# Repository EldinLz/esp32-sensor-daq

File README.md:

# ESP32 Sensor Data Acquisition Board

A custom two-layer PCB and Arduino firmware project for collecting ambient-light, temperature, humidity, and pressure data with an ESP32-C3.

> **Project status:** Rev A was hand-assembled, programmed, and hardware-validated on 2026-08-22. The ESP32-C3 streams serial CSV data, the BME280 is detected over I2C, and the MCP6002-buffered light channel responds from covered to bright-light conditions. Long-duration logging and calibrated light measurement have not been completed.

## Overview

This project combines a custom KiCad carrier board with an ESP32-C3 DevKitM-1. A photoresistor signal is conditioned by an MCP6002 op-amp and sampled by the ESP32 ADC, while a BME280 breakout provides environmental data over I2C. Six labeled test points expose the primary power and signal nets for structured bring-up and debugging.

```mermaid
flowchart LR
    LDR["Photoresistor divider"] --> OP["MCP6002 buffer"]
    OP --> ADC["ESP32-C3 GPIO0 / ADC"]
    BME["BME280 temperature, humidity, pressure"] -->|"I2C: GPIO4 SDA, GPIO5 SCL"| ESP["ESP32-C3"]
    ADC --> ESP
    ESP --> LED["Status LED on GPIO7"]
    ESP --> USB["CSV data over USB serial"]
```

## Finished hardware

The Rev A PCB was assembled by hand with the ESP32-C3 in removable socket headers and the BME280 connected through the labeled J1 I2C header.

## Key features

- ESP32-C3 DevKitM-1 controller on removable 1x15 sockets
- BME280 interface with 4.7 kOhm I2C pull-up resistors
- Photoresistor voltage divider buffered by an MCP6002 op-amp
- 100 nF local decoupling capacitor for the analog section
- Status LED with a 330 Ohm current-limiting resistor
- Six labeled test points: 3V3, GND, raw light signal, buffered ADC signal, SDA, and SCL
- CSV serial output suitable for logging or plotting
- Through-hole construction for accessible hand assembly and rework

## Pin map

| Function | ESP32-C3 pin | PCB test point or connector |
|---|---:|---|
| Light sensor ADC | GPIO0 | TP4 `ADC` |
| I2C SDA | GPIO4 | TP5 `SDA`, J1 pin 3 |
| I2C SCL | GPIO5 | TP6 `SCL`, J1 pin 4 |
| Status LED | GPIO7 | D1 through R5 |
| 3.3 V | 3V3 | TP1, J1 pin 1 |
| Ground | GND | TP2, J1 pin 2 |
| Raw light-divider signal | - | TP3 `RAW` |

## Firmware

The Arduino firmware:

1. Initializes the ESP32 ADC and the BME280 at address `0x77`, then tries `0x76` as a fallback.
2. Samples the buffered light-sensor signal once per second.
3. Reads temperature, humidity, and pressure when the BME280 is available.
4. Emits one CSV row per second at 115200 baud.

Measured Rev A serial output:

```text
BME280 detected
time_ms,light_raw,light_percent,temperature_C,humidity_percent,pressure_hPa
628,2058,50.3,25.70,47.22,1009.73
```

### Build environment

- Arduino IDE 2.3.10
- `esp32` board package by Espressif Systems 3.3.11
- Board target: `ESP32C3 Dev Module`
- Adafruit BME280 Library 2.3.0 and its installed dependencies

## Rev A hardware validation

These captured values demonstrate end-to-end operation; they are not calibration data.

| Check | Result | Captured evidence |
|---|---|---|
| Post-assembly power-off check | Pass | No 3V3-to-GND short was found. |
| 3.3 V operation | Pass | The assembled board powered and ran from the ESP32-C3 3.3 V rail. |
| Firmware and serial output | Pass | Firmware uploaded successfully and produced one 115200-baud CSV row per second. |
| BME280 I2C sensing | Pass | Serial Monitor reported `BME280 detected`; observed readings were about 25.2-26.0 C, 47-49% RH, and 1009.7-1009.9 hPa. |
| Light channel - covered | Pass | `light_raw` approximately 247-265; `light_percent` approximately 6.0-6.5%. |
| Light channel - room light | Pass | `light_raw` approximately 1887-2134; `light_percent` approximately 46.1-52.1%. |
| Light channel - flashlight | Pass | `light_raw` = 4095; `light_percent` = 100.0%. |
| Status LED | Pass | A brief firmware-driven activity blink was observed. |

`light_percent` is the 12-bit ADC reading normalized to full scale; it is not a calibrated lux measurement. The light tests validate the complete photoresistor-divider, MCP6002-buffer, ADC, firmware, and serial-output path, but do not independently characterize the op-amp transfer function.

See [VALIDATION.md](docs/VALIDATION.md) for the full validation record and [TEST_PLAN.md](docs/TEST_PLAN.md) for the staged bring-up procedure.

## Repository structure

```text
.
├── fabrication/  Final Gerber and drill archive used for PCB ordering
├── firmware/     Arduino sketch folder and firmware source
├── hardware/     KiCad schematic, PCB, and project files
├── images/       KiCad renders and finished Rev A build photos
└── docs/         BOM, validation record, test plan, and resume notes
```

## Design and validation status

- KiCad schematic ERC: 0 errors and 0 warnings
- KiCad PCB Editor DRC: 0 errors; one expected footprint/library mismatch warning after the ESP32 socket-pad customization
- Unrouted connections: 0
- Gerber and drill archive generated; PCB fabrication and delivery complete
- Rev A assembly, soldering, post-assembly short check, firmware upload, and serial output: complete
- BME280 I2C sensing and end-to-end light-channel response: hardware-validated

## Optional follow-on characterization

- Run and archive a one-hour serial logging test
- Measure TP3 (`RAW`) and TP4 (`ADC`) simultaneously to quantify buffer tracking
- Calibrate the light channel against a lux reference if absolute illumination is required

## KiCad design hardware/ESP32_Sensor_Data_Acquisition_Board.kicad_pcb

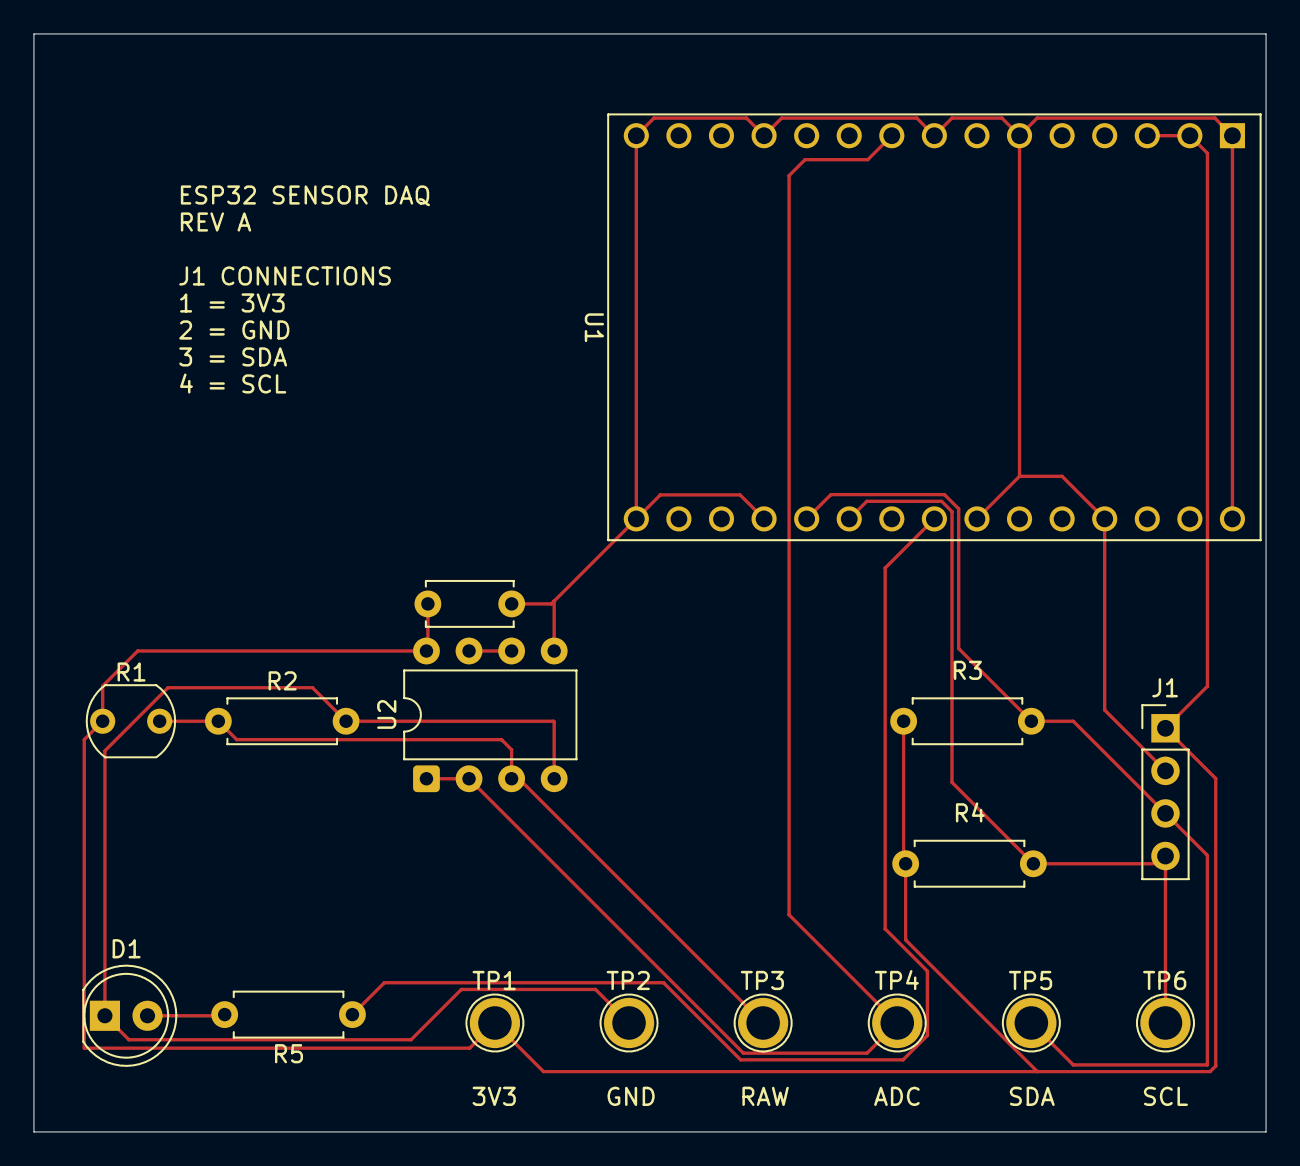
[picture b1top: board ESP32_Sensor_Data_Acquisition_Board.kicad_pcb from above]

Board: 2 copper layers, 73.5 x 65.5 mm, 16 parts (0 on the bottom side), 9 nets.

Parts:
C1: 100nF; C_Disc_D5.0mm_W2.5mm_P5.00mm
D1: LED; LED_D5.0mm
J1: BME280; PinHeader_1x04_P2.54mm_Vertical
R1: R_Photo; R_LDR_5.1x4.3mm_P3.4mm_Vertical
R2: 10k; R_Axial_DIN0207_L6.3mm_D2.5mm_P7.62mm_Horizontal
R3, R4: 4.7k; R_Axial_DIN0207_L6.3mm_D2.5mm_P7.62mm_Horizontal
R5: 330; R_Axial_DIN0207_L6.3mm_D2.5mm_P7.62mm_Horizontal
TP1, TP2, TP3, TP4, TP5, TP6: TestPoint; TestPoint_Plated_Hole_D2.0mm
U1: ESP32-C3-DevKitM-1
U2: MCP6002-xP; DIP-8_W7.62mm

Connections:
+3V3: C1.1, J1.1, R1.1, R3.1, R4.1, TP1.1 (1_1), U1.2 (3V3), U1.3 (3V3), U2.8 (V+)
/I2C_SCL: J1.4, R4.2, TP6.1 (1_1), U1.21 (IO5)
/I2C_SDA: J1.3, R3.2, TP5.1 (1_1), U1.20 (IO4)
/LIGHT_ADC: TP4.1 (1_1), U1.9 (IO0), U2.1, U2.2 (-)
/LIGHT_RAW: R1.2, R2.1, TP3.1 (1_1), U2.3 (+)
/STATUS_LED: R5.1, U1.23 (IO7)
GND: C1.2, D1.1 (K), J1.2, R2.2, TP2.1 (1_1), U1.1 (GND), U1.6 (GND), U1.8 (GND), U1.12 (GND), U1.15 (GND), U1.16 (GND), U1.19 (GND), U1.24 (GND), U1.27 (GND), U1.30 (GND), U2.4 (V-), U2.5 (+)
unnamed: D1.2 (A), R5.2
unnamed: U2.6 (-), U2.7

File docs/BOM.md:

# Bill of Materials

Quantities below are for one assembled board. Exact supplier stock can change; verify the footprint, lead pitch, and voltage rating before substituting a part.

| Ref. | Qty. | Component | Value / selected part | PCB footprint or interface |
|---|---:|---|---|---|
| U1 | 1 | ESP32-C3 development board | ESP32-C3 DevKitM-1 | Two 1x15, 2.54 mm socket rows |
| U2 | 1 | Dual rail-to-rail op-amp | MCP6002-I/P | DIP-8, 7.62 mm row spacing |
| — | 1 | DIP socket | 8-position | DIP-8 |
| R1 | 1 | CdS photoresistor | 5 mm class | 3.4 mm lead pitch footprint |
| R2 | 1 | Resistor | 10 kΩ, 1/4 W | Axial, 7.62 mm pitch |
| R3, R4 | 2 | I2C pull-up resistors | 4.7 kΩ, 1/4 W | Axial, 7.62 mm pitch |
| R5 | 1 | LED resistor | 330 Ω, 1/4 W | Axial, 7.62 mm pitch |
| C1 | 1 | Ceramic capacitor | 100 nF | Through-hole disc, 5.00 mm pitch |
| D1 | 1 | Status LED | 5 mm LED | 2.54 mm pitch |
| J1 | 1 | BME280 connector | 1x4 vertical pin header | 2.54 mm pitch |
| — | 1 | BME280 breakout | Adafruit BME280 I2C/SPI breakout | Connected to J1 over 3V3, GND, SDA, SCL |
| — | 2 | ESP32 socket strips | 1x15 female receptacle | 2.54 mm pitch |

## Test points

TP1 through TP6 are plated through-holes and do not require a separate component. Optional loop or turret test points may be installed if desired.

| Test point | Net |
|---|---|
| TP1 | 3V3 |
| TP2 | GND |
| TP3 | LIGHT_RAW |
| TP4 | LIGHT_ADC |
| TP5 | I2C_SDA |
| TP6 | I2C_SCL |

## Assembly supplies

- Solder and flux
- Female-to-female jumper wires for the BME280 breakout
- USB data cable for ESP32 programming
- Multimeter with continuity and DC-voltage modes
